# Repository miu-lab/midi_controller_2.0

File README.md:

# MIDI Controller

MIDI Controller est un projet de contrôleur MIDI pour la plateforme Teensy, utilisant PlatformIO pour la gestion du projet et la compilation. Il offre une architecture modulaire et extensible pour le développement d'applications de contrôle MIDI.

## Vue d'ensemble

Ce projet implémente un contrôleur MIDI complet avec:
- Support pour encodeurs rotatifs, boutons et autres contrôles
- Affichage OLED pour l'interface utilisateur
- Communication MIDI via USB
- Gestion de profils et configurations personnalisables

## Architecture

Le projet est organisé selon une architecture hexagonale (aussi appelée architecture en oignon) avec injection de dépendances:

### Couches Principales

- **Core** : Contient la logique métier principale, indépendante de l'implémentation
  - **Domain** : Définitions des entités et interfaces principales
  - **Use Cases** : Implémentation des cas d'utilisation
  - **Ports** : Interfaces pour les adaptateurs
  - **Interfaces** : Contrats abstraits pour les sous-systèmes

- **Adapters** : Implémentations concrètes des interfaces
  - **Primary** : Adaptateurs d'entrée (UI, contrôles)
  - **Secondary** : Adaptateurs de sortie (MIDI, stockage)

- **App** : Point d'entrée de l'application et orchestration
  - **Subsystems** : Sous-systèmes modulaires encapsulant des fonctionnalités complètes
  - **DI** : Système d'injection de dépendances moderne

### Sous-systèmes

L'application est divisée en sous-systèmes indépendants, chacun implémentant une interface abstraite:

- **ConfigurationSubsystem** (`IConfiguration`): Gestion des paramètres et préférences
- **InputSubsystem** (`IInputSystem`): Traitement des entrées utilisateur
- **MidiSubsystem** (`IMidiSystem`): Communication MIDI et mapping
- **UISubsystem** (`IUISystem`): Interface utilisateur et affichage

## Fonctionnalités Principales

- **Mapping MIDI flexible**: Assignez facilement des contrôles à différents messages MIDI
- **Interface utilisateur intuitive**: Navigation par menus sur écran OLED
- **Profils multiples**: Sauvegardez et chargez différentes configurations
- **Mode d'apprentissage**: Apprenez facilement de nouveaux mappings MIDI
- **Modularité**: Ajoutez de nouvelles fonctionnalités sans modifier le code existant

## Compilation et Déploiement

### Prérequis
- PlatformIO
- Teensy Loader
- Librairies Arduino requises (voir platformio.ini)

### Compilation
```bash
pio run
```

### Upload vers le Teensy
```bash
pio run -t upload
```

### Moniteur Série
```bash
pio device monitor
```

## Tests

Le projet comprend une infrastructure de tests unitaires et d'intégration basée sur Unity:

```bash
pio test
```

Les tests couvrent les composants individuels ainsi que l'intégration des sous-systèmes.

## Contribution

Les contributions sont les bienvenues! Veuillez consulter [CONTRIBUTING.md](CONTRIBUTING.md) pour les lignes directrices sur la façon de contribuer au projet.

## Licence

Ce projet est sous licence MIT. Voir le fichier LICENSE pour plus de détails.

## Contact

Pour toute question ou suggestion, veuillez ouvrir une issue sur le dépôt GitHub du projet.

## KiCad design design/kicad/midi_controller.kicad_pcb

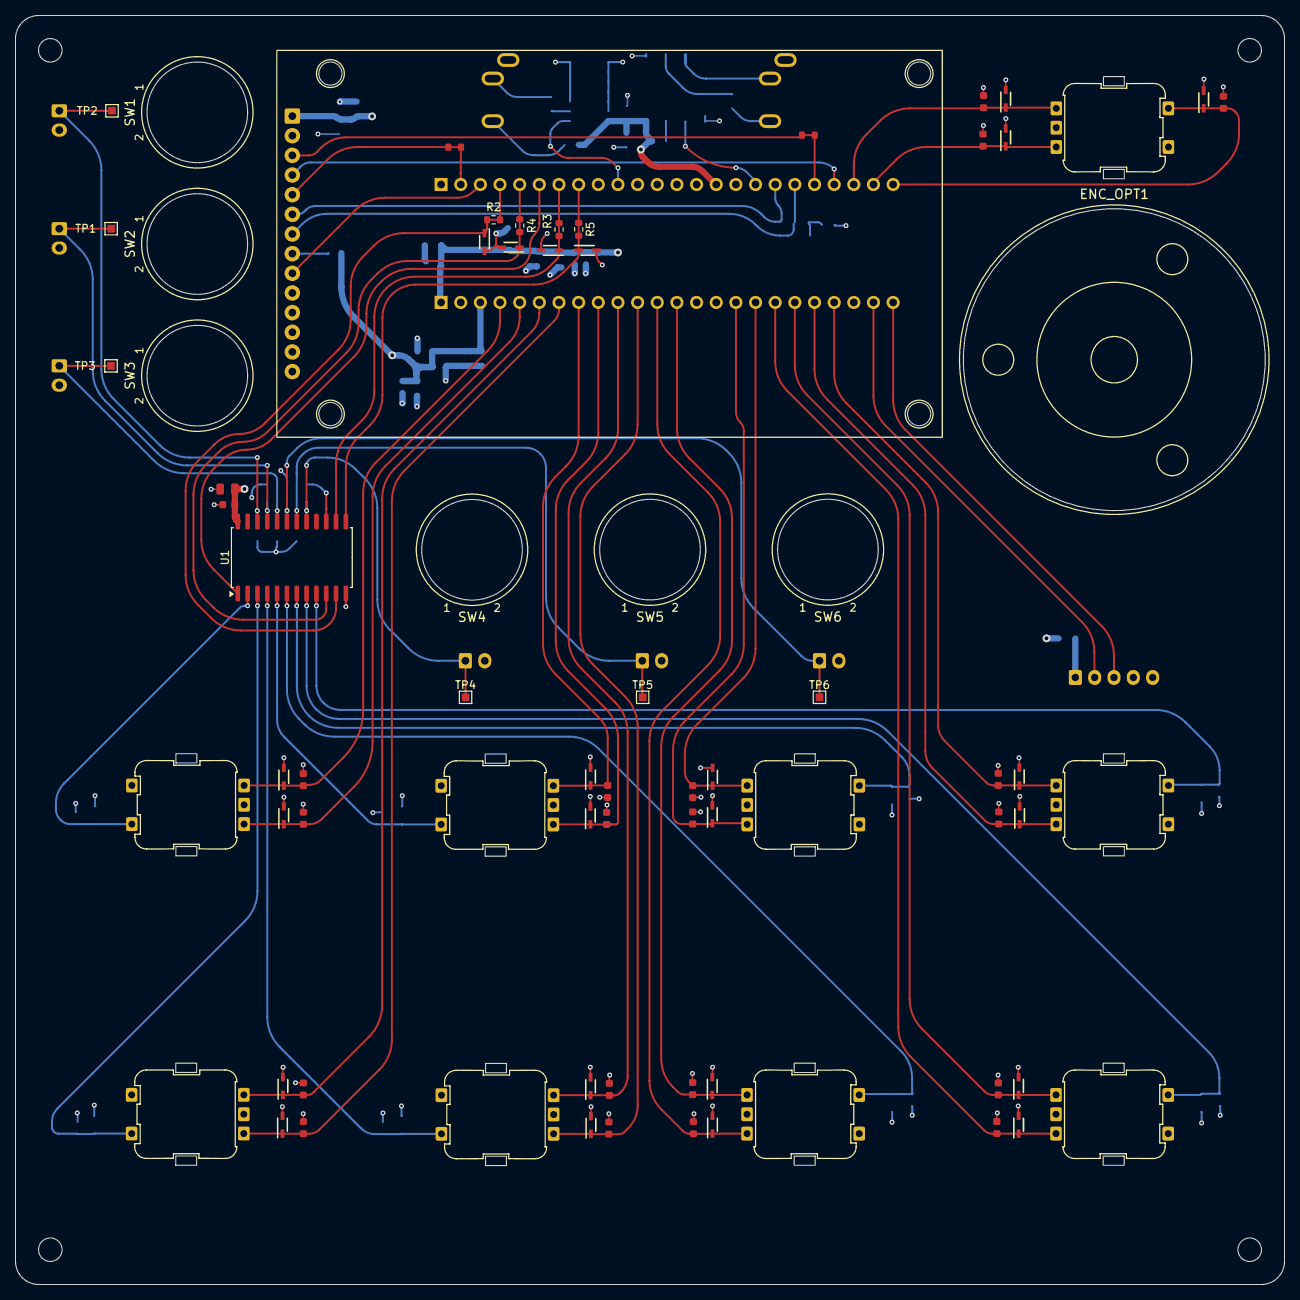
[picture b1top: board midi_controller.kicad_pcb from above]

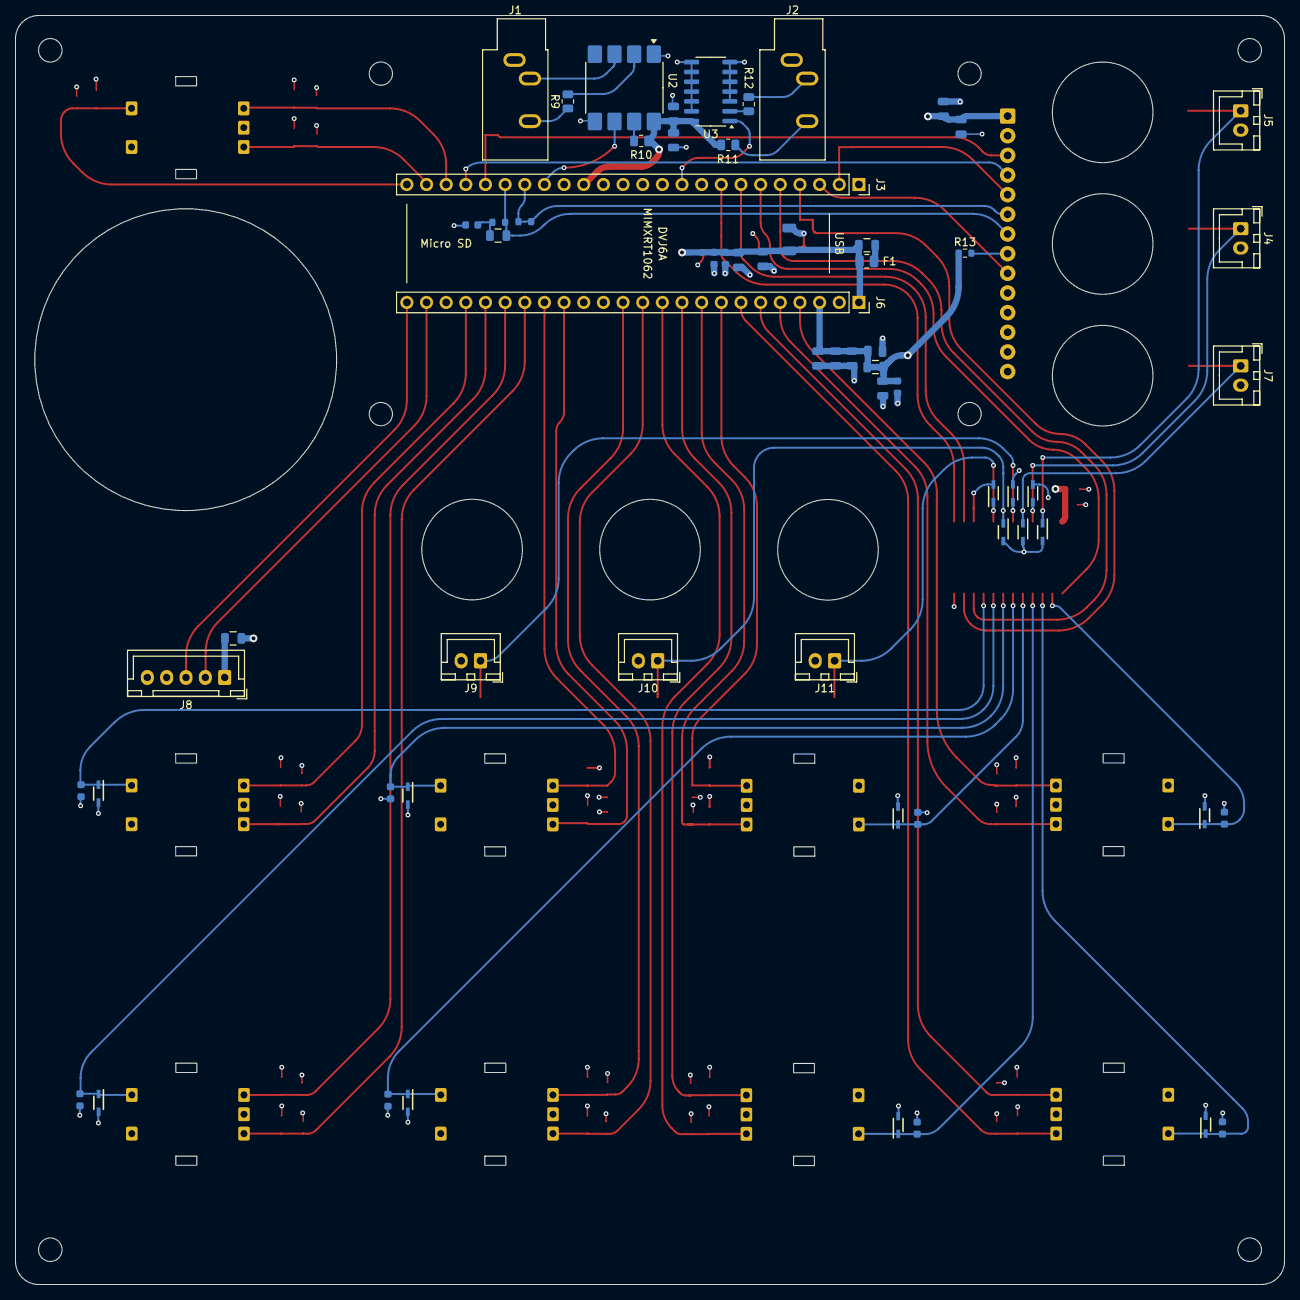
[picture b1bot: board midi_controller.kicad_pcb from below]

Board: 4 copper layers, 164.0 x 164.0 mm, 138 parts (64 on the bottom side), 63 nets.

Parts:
C1, C2, C3, C5, C6, C7, C8, C9, C10, C11, C12, C13, C14, C15, C16, C17, C18, C19, C20, C21, C38, C39, C40, C41, C42, C43, C44, C45: 100nF; C_0603
C4, C31, C35: 10uF; C_0805
C22: 100pF; C_0603
C23: 100uF; C_1206
C24, C37: 1nF; C_0603
C25, C26, C28, C30, C32, C34, C36: 100nF; C_0805
C27, C33: 47uF; C_0805
C29: 10nF; C_0603
D1, D2, D3, D4, D5, D6, D7, D8, D9, D10, D11, D12, D13, D14, D15, D16, D17, D18, D19, D20, D21, D22, D23, D24, D25, D26, D27, D28, D29, D30, D31, D32, D33, D34, D35, D36, D37: PESD5V0L1BA,115; SOD2512X110N
DISP1: MIDI_Display_MSP2807; MSP2807_ILI9341_Display
ENC_MECH1, ENC_MECH2, ENC_MECH3, ENC_MECH4, ENC_MECH5, ENC_MECH6, ENC_MECH7, ENC_MECH8, ENC_MECH9: MIDI_Encoder_PEC11R; PEC11R4220FS0024
ENC_OPT1: MIDI_Encoder_E38S6G5_Optical; E38S6G5_Optical_Encoder
F1: Fuse; Fuse_0805_2012Metric
FB1, FB2, FB3, FB4: FB_0805
J1: MIDI In; Jack_3.5mm_CUI_SJ1-3533NG_Horizontal
J2: MIDI Out; Jack_3.5mm_CUI_SJ1-3533NG_Horizontal
J3, J6: Conn_01x24_Socket; PinSocket_1x24_P2.54mm_Vertical
J4, J5, J7, J9, J10, J11: Conn_01x02_Socket; JST_XH_B2B-XH-A_1x02_P2.50mm_Vertical_JLC_Constraints
J8: Conn_01x05; JST_XH_B5B-XH-A_1x05_P2.50mm_Vertical
MCU1: MIDI_Teensy4.1; Teensy41_Mechanical
R1, R6, R7, R8: 33Ω; R_0603
R2, R3, R4, R5: 100; R_0603_1608Metric
R9, R11, R12: 220; R_0805_2012Metric
R10: 1k; R_0805_2012Metric
R13: 220; R_0603_1608Metric
SW1, SW2, SW3, SW4, SW5, SW6: PV0H24011_Pushbutton
TP1, TP2, TP3, TP4, TP5, TP6: TestPoint; TestPoint_Pad_1.0x1.0mm
U1: CD74HC4067M; SOIC-24W_7.5x15.4mm_P1.27mm
U2: 6N137; SOP-8_6.605x9.655mm_P2.54mm
U3: 74HC14D,653; SOIC-14_L8.7-W3.9-P1.27-LS6.0-BL

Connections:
+3V3_A: C4.1, C5.1, C32.1, C33.1, C34.1, C35.1, C36.1, C37.1, FB3.1, FB3.2, J6.3, R13.1, U1.24 (VCC)
+3V3_B: C26.1, C28.2, J3.15, R10.2, R11.1, U2.8 (VCC), U3.14 (VCC)
+5V: C23.1, C24.1, C25.1, C27.1, C29.1, C30.2, C31.1, DISP1.1 (VCC), F1.1, FB2.1, FB4.2, J6.1
/Buttons_Momentary/BUTTON_PUSH_MOM_01: D26.1 (K1), J5.1, TP2.1, U1.22 (I9)
/Buttons_Momentary/BUTTON_PUSH_MOM_02: D29.1 (K1), J4.1, TP1.1, U1.21 (I10)
/Buttons_Momentary/BUTTON_PUSH_MOM_03: D28.1 (K1), J7.1, TP3.1, U1.20 (I11)
/Buttons_Momentary/BUTTON_PUSH_MOM_04: D27.1 (K1), J9.1, TP6.1, U1.19 (I12)
/Buttons_Momentary/BUTTON_PUSH_MOM_05: D24.1 (K1), J10.1, TP5.1, U1.18 (I13)
/Buttons_Momentary/BUTTON_PUSH_MOM_06: D25.1 (K1), J11.1, TP4.1, U1.17 (I14)
/COM: J3.6, U1.1 (COM)
/CS: DISP1.3 (CS), J3.20, R6.1, R6.2
/DC: DISP1.5 (DC), J3.2, R1.1, R1.2
/LED: DISP1.8 (LED), R13.2
/MIDI_Encoder_Matrix_2x4_with_push_buttons/1x1.QUAD_A: C7.2, D9.1 (K1), ENC_MECH2.A, J6.5
/MIDI_Encoder_Matrix_2x4_with_push_buttons/1x1.QUAD_B: C6.2, D8.1 (K1), ENC_MECH2.B, J6.4
/MIDI_Encoder_Matrix_2x4_with_push_buttons/1x1_SW_A: C41.2, D33.1 (K1), ENC_MECH2.1 (SW1), U1.2 (I7)
/MIDI_Encoder_Matrix_2x4_with_push_buttons/1x2.QUAD_A: C8.2, D11.1 (K1), ENC_MECH3.A, J6.9
/MIDI_Encoder_Matrix_2x4_with_push_buttons/1x2.QUAD_B: C9.2, D10.1 (K1), ENC_MECH3.B, J6.8
/MIDI_Encoder_Matrix_2x4_with_push_buttons/1x2_SW_A: C40.2, D32.1 (K1), ENC_MECH3.1 (SW1), U1.5 (I4)
/MIDI_Encoder_Matrix_2x4_with_push_buttons/1x3.QUAD_A: C10.2, D12.1 (K1), ENC_MECH4.A, J6.17
/MIDI_Encoder_Matrix_2x4_with_push_buttons/1x3.QUAD_B: C11.2, D13.1 (K1), ENC_MECH4.B, J6.16
/MIDI_Encoder_Matrix_2x4_with_push_buttons/1x3_SW_A: C39.2, D31.1 (K1), ENC_MECH4.1 (SW1), U1.7 (I2)
/MIDI_Encoder_Matrix_2x4_with_push_buttons/1x4.QUAD_A: C12.2, D14.1 (K1), ENC_MECH5.A, J6.21
/MIDI_Encoder_Matrix_2x4_with_push_buttons/1x4.QUAD_B: C13.2, D15.1 (K1), ENC_MECH5.B, J6.20
/MIDI_Encoder_Matrix_2x4_with_push_buttons/1x4_SW_A: C38.2, D30.1 (K1), ENC_MECH5.1 (SW1), U1.9 (I0)
/MIDI_Encoder_Matrix_2x4_with_push_buttons/2x1.QUAD_A: C14.2, D17.1 (K1), ENC_MECH6.A, J6.7
/MIDI_Encoder_Matrix_2x4_with_push_buttons/2x1.QUAD_B: C15.2, D16.1 (K1), ENC_MECH6.B, J6.6
/MIDI_Encoder_Matrix_2x4_with_push_buttons/2x1_SW_A: C45.2, D37.1 (K1), ENC_MECH6.1 (SW1), U1.3 (I6)
/MIDI_Encoder_Matrix_2x4_with_push_buttons/2x2.QUAD_A: C16.2, D18.1 (K1), ENC_MECH7.A, J6.11
/MIDI_Encoder_Matrix_2x4_with_push_buttons/2x2.QUAD_B: C17.2, D19.1 (K1), ENC_MECH7.B, J6.10
/MIDI_Encoder_Matrix_2x4_with_push_buttons/2x2_SW_A: C44.2, D36.1 (K1), ENC_MECH7.1 (SW1), U1.4 (I5)
/MIDI_Encoder_Matrix_2x4_with_push_buttons/2x3.QUAD_A: C19.2, D20.1 (K1), ENC_MECH8.A, J6.13
/MIDI_Encoder_Matrix_2x4_with_push_buttons/2x3.QUAD_B: C18.2, D21.1 (K1), ENC_MECH8.B, J6.12
/MIDI_Encoder_Matrix_2x4_with_push_buttons/2x3_SW_A: C43.2, D35.1 (K1), ENC_MECH8.1 (SW1), U1.6 (I3)
/MIDI_Encoder_Matrix_2x4_with_push_buttons/2x4.QUAD_A: C20.2, D22.1 (K1), ENC_MECH9.A, J6.19
/MIDI_Encoder_Matrix_2x4_with_push_buttons/2x4.QUAD_B: C21.2, D23.1 (K1), ENC_MECH9.B, J6.18
/MIDI_Encoder_Matrix_2x4_with_push_buttons/2x4_SW_A: C42.2, D34.1 (K1), ENC_MECH9.1 (SW1), U1.8 (I1)
/MISO: DISP1.9 (SDO/MISO), J3.3
/MOSI: DISP1.6 (SDI/MOSI), J3.18, R8.1, R8.2
/NAV.QUAD_A: C1.2, D1.1 (K1), ENC_MECH1.A, J3.22
/NAV.QUAD_B: C2.2, D7.1 (K1), ENC_MECH1.B, J3.23
/NAV.SW: C3.2, D2.1 (K1), ENC_MECH1.1 (SW1), J3.24
/OPT.QUAD_A: J6.23, J8.2
/OPT.QUAD_B: J6.24, J8.3
/RST: DISP1.4 (RST), J3.21
/RX6: J3.17, U2.6 (VO)
/S0: D5.1 (K1), J3.5, R4.1, R4.2, U1.10 (S0)
/S1: D3.1 (K1), J3.4, R2.1, R2.2, U1.11 (S1)
/S2: D6.1 (K1), J3.7, R3.1, R3.2, U1.14 (S2)
/S3: D4.1 (K1), J3.8, R5.1, R5.2, U1.13 (S3)
/SCK: DISP1.7 (SCK), FB1.1, J3.19, R7.2
/TX2: J3.10, U3.1 (1A)
GND: C1.1, C2.1, C3.1, C4.2, C5.2, C6.1, C7.1, C8.1, C9.1, C10.1, C11.1, C12.1, C13.1, C14.1, C15.1, C16.1, C17.1, C18.1, C19.1, C20.1, C21.1, C22.2, C23.2, C24.2, C25.2, C26.2, C27.2, C28.1, C29.2, C30.1, C31.2, C32.2, C33.2, C34.2, C35.2, C36.2, C37.2, C38.1, C39.1, C40.1, C41.1, C42.1, C43.1, C44.1, C45.1, D1.2 (K2), D2.2 (K2), D3.2 (K2), D4.2 (K2), D5.2 (K2), D6.2 (K2), D7.2 (K2), D8.2 (K2), D9.2 (K2), D10.2 (K2), D11.2 (K2), D12.2 (K2), D13.2 (K2), D14.2 (K2), D15.2 (K2), D16.2 (K2), D17.2 (K2), D18.2 (K2), D19.2 (K2), D20.2 (K2), D21.2 (K2), D22.2 (K2), D23.2 (K2), D24.2 (K2), D25.2 (K2), D26.2 (K2), D27.2 (K2), D28.2 (K2), D29.2 (K2), D30.2 (K2), D31.2 (K2), D32.2 (K2), D33.2 (K2), D34.2 (K2), D35.2 (K2), D36.2 (K2), D37.2 (K2), DISP1.2 (GND), ENC_MECH1.2 (GND), ENC_MECH1.C (GND), ENC_MECH2.2 (GND), ENC_MECH2.C (GND), ENC_MECH3.2 (GND), ENC_MECH3.C (GND), ENC_MECH4.2 (GND), ENC_MECH4.C (GND), ENC_MECH5.2 (GND), ENC_MECH5.C (GND), ENC_MECH6.2 (GND), ENC_MECH6.C (GND), ENC_MECH7.2 (GND), ENC_MECH7.C (GND), ENC_MECH8.2 (GND), ENC_MECH8.C (GND), ENC_MECH9.2 (GND), ENC_MECH9.C (GND), J1.S, J2.S, J3.1, J4.2, J5.2, J6.2, J6.15, J7.2, J8.4, J8.5, J9.2, J10.2, J11.2, U1.12 (GND), U1.15 (~E), U2.1 (NC), U2.5 (GND), U3.3 (2A), U3.4 (2Y), U3.5 (3A), U3.6 (3Y), U3.7 (GND), U3.8 (4Y), U3.9 (4A), U3.10 (5Y), U3.11 (5A), U3.12 (6Y), U3.13 (6A)
unnamed: C22.1, FB1.2, R7.1
unnamed: F1.2, FB2.2
unnamed: J1.R, R9.1
unnamed: J2.R, R11.2
unnamed: J2.T, R12.2
unnamed: FB4.1, J8.1
unnamed: R9.2, U2.2 (A)
unnamed: J1.T, U2.3 (C)
unnamed: R10.1, U2.7 (EN)
unnamed: R12.1, U3.2 (1Y)

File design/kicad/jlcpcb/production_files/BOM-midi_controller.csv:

Comment,Designator,Footprint,LCSC,Quantity
~,"FB1,FB2,FB3,FB4",FB_0805,C1015,4
100nF,"C1,C10,C11,C12,C13,C14,C15,C16,C17,C18,C19,C2,C20,C21,C3,C38,C39,C40,C41,C42,C43,C44,C45,C5,C6,C7,C8,C9",C_0603,C14663,28
100pF,C22,C_0603,C14858,1
100uF,C23,C_1206,C15008,1
6N137,U2,SOP-8_6.605x9.655mm_P2.54mm,C15825,1
10uF,"C31,C35,C4",C_0805,C15850,3
1nF,"C24,C37",C_0603,C1588,2
47uF,"C27,C33",C_0805,C16780,2
1k,R10,R_0805_2012Metric,C17513,1
220,"R11,R12,R9",R_0805_2012Metric,C17557,3
100,"R2,R3,R4,R5",R_0603_1608Metric,C22775,4
220,R13,R_0603_1608Metric,C22962,1
33Ω,"R1,R6,R7,R8",R_0603,C23140,4
100nF,"C25,C26,C28,C30,C32,C34,C36",C_0805,C28233,7
Conn_01x02_Socket,"J10,J11,J4,J5,J7,J9",JST_XH_B2B-XH-A_1x02_P2.50mm_Vertical_JLC_Constraints,C2908600,6
Conn_01x05,J8,JST_XH_B5B-XH-A_1x05_P2.50mm_Vertical,C2908603,1
Conn_01x24_Socket,"J3,J6",PinSocket_1x24_P2.54mm_Vertical,C41376163,2
CD74HC4067M,U1,SOIC-24W_7.5x15.4mm_P1.27mm,C496123,1
"74HC14D,653",U3,SOIC-14_L8.7-W3.9-P1.27-LS6.0-BL,C5605,1
10nF,C29,C_0603,C57112,1
"PESD5V0L1BA,115","D1,D10,D11,D12,D13,D14,D15,D16,D17,D18,D19,D2,D20,D21,D22,D23,D24,D25,D26,D27,D28,D29,D3,D30,D31,D32,D33,D34,D35,D36,D37,D4,D5,D6,D7,D8,D9",SOD2512X110N,C85380,37
Fuse,F1,Fuse_0805_2012Metric,C883101,1

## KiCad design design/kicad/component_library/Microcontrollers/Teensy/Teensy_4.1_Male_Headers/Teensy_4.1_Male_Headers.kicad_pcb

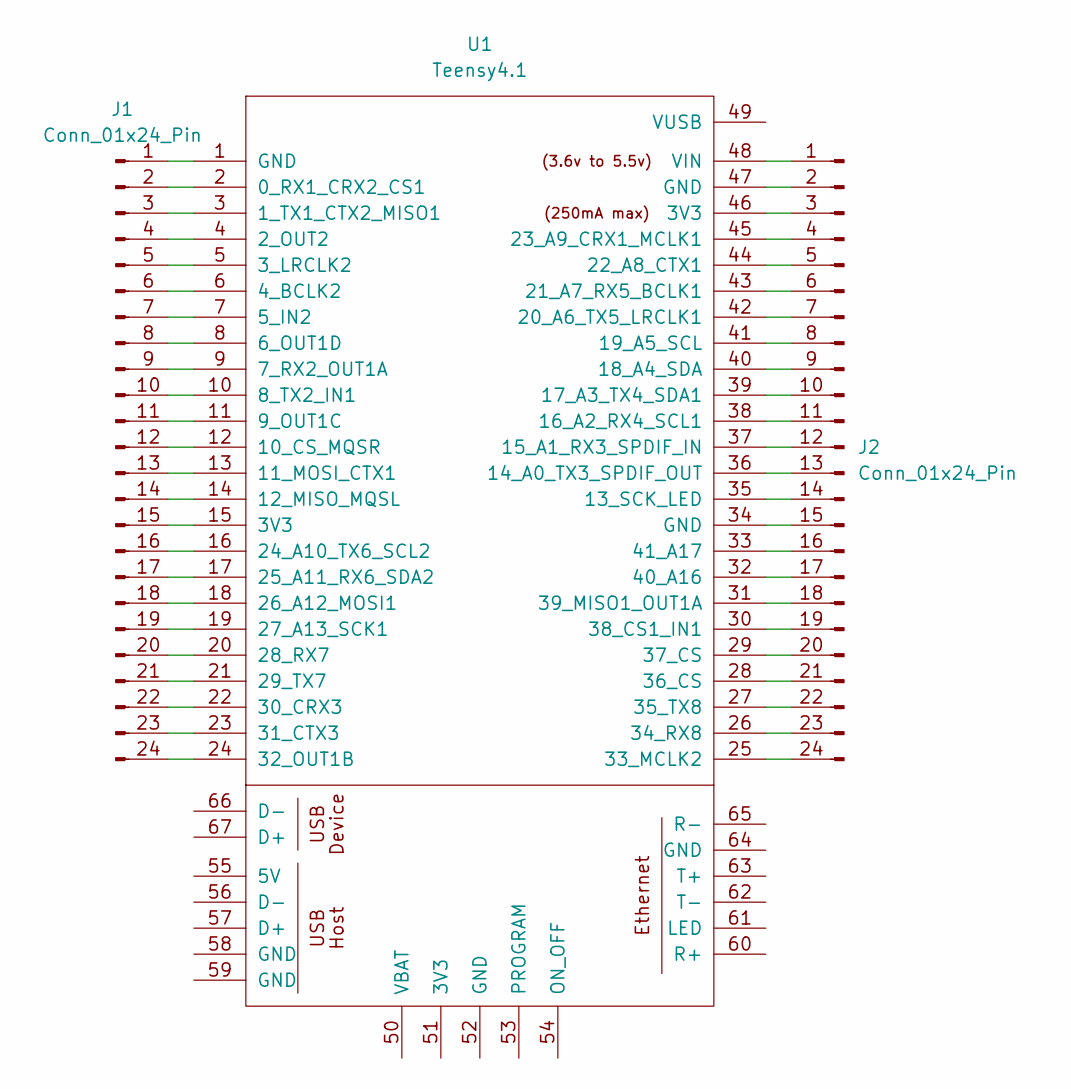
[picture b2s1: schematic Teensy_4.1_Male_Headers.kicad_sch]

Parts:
J1, J2: Conn_01x24_Pin; PinHeader_1x24_P2.54mm_Vertical
U1: Teensy4.1; Teensy41

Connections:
unnamed: J1.1, U1.1 (GND)
unnamed: J1.2, U1.2 (0_RX1_CRX2_CS1)
unnamed: J1.3, U1.3 (1_TX1_CTX2_MISO1)
unnamed: J1.4, U1.4 (2_OUT2)
unnamed: J1.5, U1.5 (3_LRCLK2)
unnamed: J1.6, U1.6 (4_BCLK2)
unnamed: J1.7, U1.7 (5_IN2)
unnamed: J1.8, U1.8 (6_OUT1D)
unnamed: J1.9, U1.9 (7_RX2_OUT1A)
unnamed: J1.10, U1.10 (8_TX2_IN1)
unnamed: J1.11, U1.11 (9_OUT1C)
unnamed: J1.12, U1.12 (10_CS_MQSR)
unnamed: J1.13, U1.13 (11_MOSI_CTX1)
unnamed: J1.14, U1.14 (12_MISO_MQSL)
unnamed: J1.15, U1.15 (3V3)
unnamed: J1.16, U1.16 (24_A10_TX6_SCL2)
unnamed: J1.17, U1.17 (25_A11_RX6_SDA2)
unnamed: J1.18, U1.18 (26_A12_MOSI1)
unnamed: J1.19, U1.19 (27_A13_SCK1)
unnamed: J1.20, U1.20 (28_RX7)
unnamed: J1.21, U1.21 (29_TX7)
unnamed: J1.22, U1.22 (30_CRX3)
unnamed: J1.23, U1.23 (31_CTX3)
unnamed: J1.24, U1.24 (32_OUT1B)
unnamed: J2.1, U1.48 (VIN)
unnamed: J2.2, U1.47 (GND)
unnamed: J2.3, U1.46 (3V3)
unnamed: J2.4, U1.45 (23_A9_CRX1_MCLK1)
unnamed: J2.5, U1.44 (22_A8_CTX1)
unnamed: J2.6, U1.43 (21_A7_RX5_BCLK1)
unnamed: J2.7, U1.42 (20_A6_TX5_LRCLK1)
unnamed: J2.8, U1.41 (19_A5_SCL)
unnamed: J2.9, U1.40 (18_A4_SDA)
unnamed: J2.10, U1.39 (17_A3_TX4_SDA1)
unnamed: J2.11, U1.38 (16_A2_RX4_SCL1)
unnamed: J2.12, U1.37 (15_A1_RX3_SPDIF_IN)
unnamed: J2.13, U1.36 (14_A0_TX3_SPDIF_OUT)
unnamed: J2.14, U1.35 (13_SCK_LED)
unnamed: J2.15, U1.34 (GND)
unnamed: J2.16, U1.33 (41_A17)
unnamed: J2.17, U1.32 (40_A16)
unnamed: J2.18, U1.31 (39_MISO1_OUT1A)
unnamed: J2.19, U1.30 (38_CS1_IN1)
unnamed: J2.20, U1.29 (37_CS)
unnamed: J2.21, U1.28 (36_CS)
unnamed: J2.22, U1.27 (35_TX8)
unnamed: J2.23, U1.26 (34_RX8)
unnamed: J2.24, U1.25 (33_MCLK2)

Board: 2 copper layers, 3 parts (2 on the bottom side), 48 nets, no tracks yet.

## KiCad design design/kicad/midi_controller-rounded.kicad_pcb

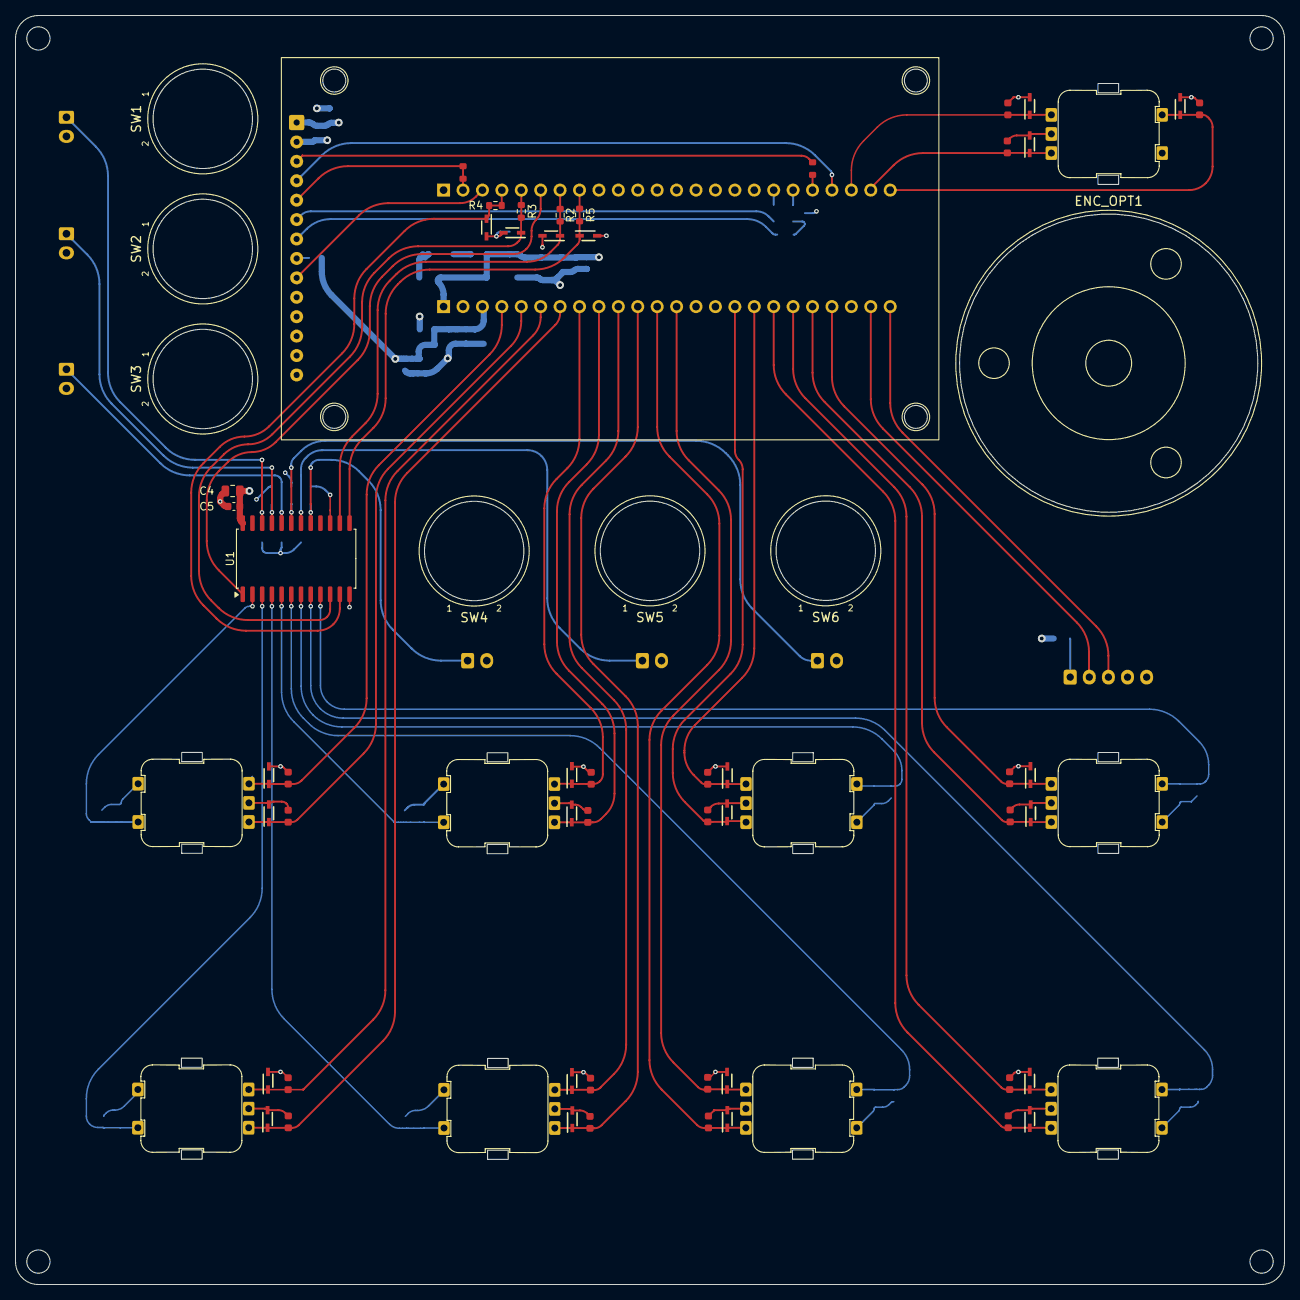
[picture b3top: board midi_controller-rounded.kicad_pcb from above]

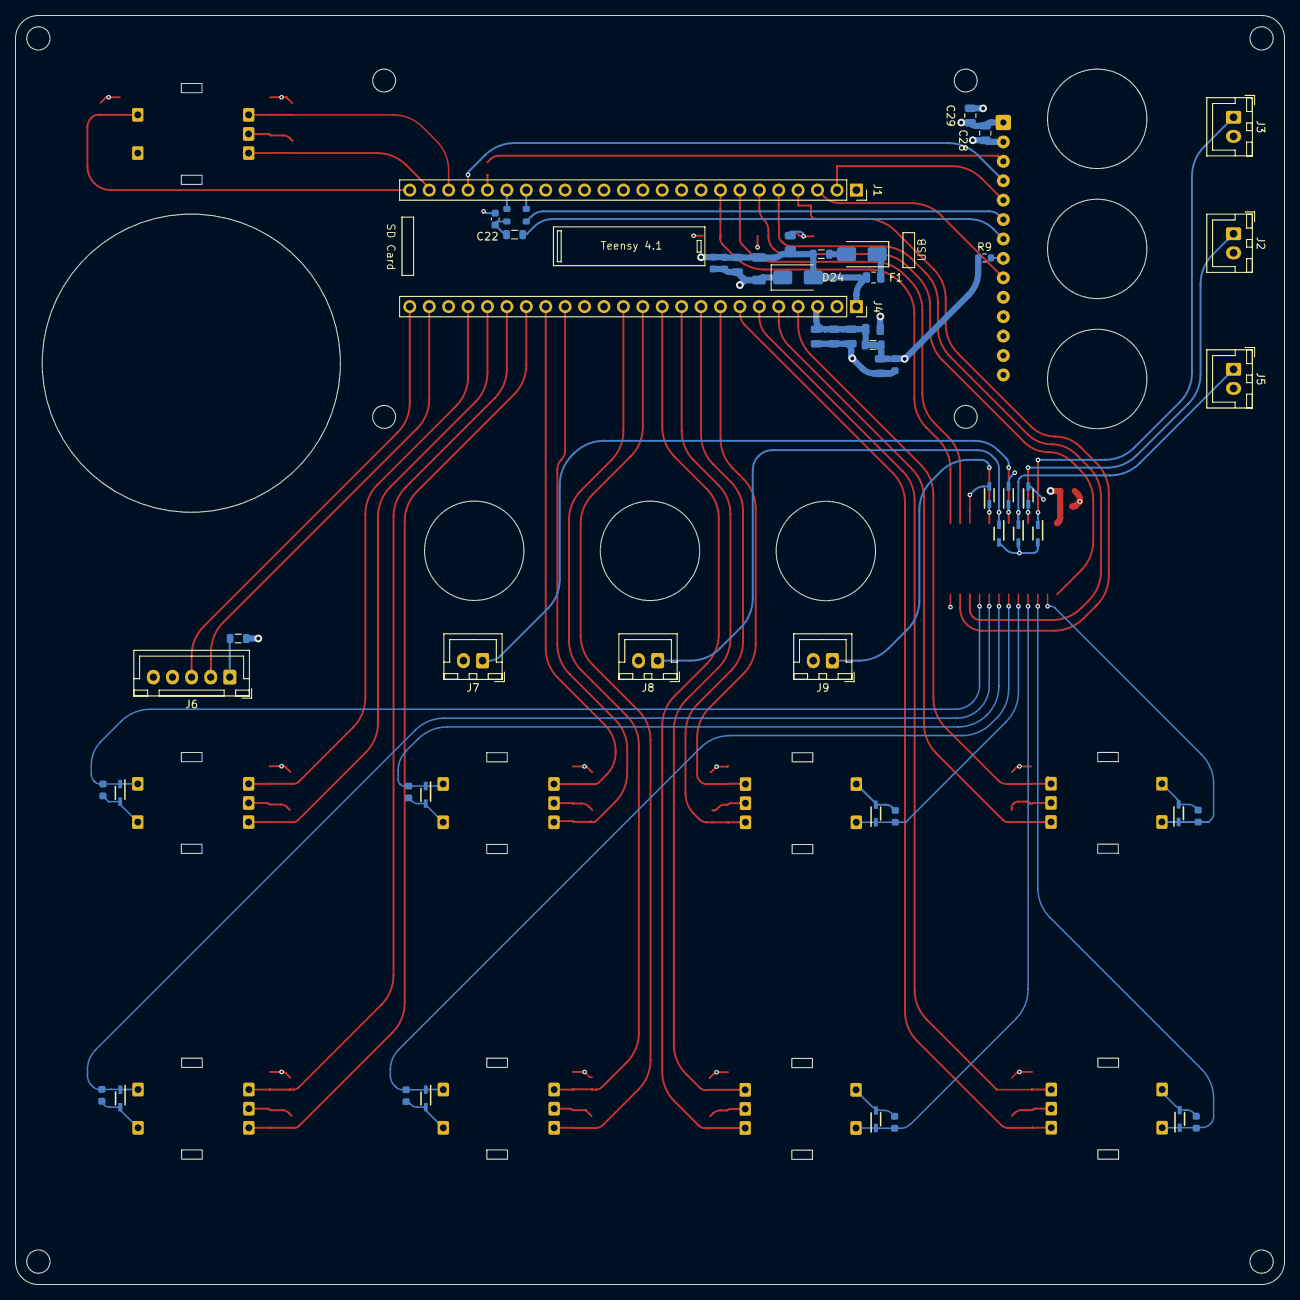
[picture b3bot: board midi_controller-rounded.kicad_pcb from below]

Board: 4 copper layers, 166.0 x 166.0 mm, 123 parts (55 on the bottom side), 57 nets.

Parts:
C1, C2, C3, C6, C7, C8, C9, C10, C11, C12, C13, C14, C15, C16, C17, C18, C19, C20, C21, C36, C37, C38, C39, C40, C41, C42, C43: 100nF; C_0603
C4, C29: 10u; C_0805_2012Metric
C5: 100n; C_0603_1608Metric
C22: 100p; C_0603_1608Metric
C23, C32, C33, C35: 100nF; C_0805
C24: 10nF; C_0603
C25, C31: 47uF; C_0805
C26: 100uF; C_1206
C27, C34: 1nF; C_0603
C28: 100n; C_0805_2012Metric
C30: 10uF; C_0805
D1, D2, D3, D4, D5, D6, D7, D8, D9, D10, D11, D12, D13, D14, D15, D16, D17, D18, D19, D20, D21, D22, D23, D26, D27, D28, D29, D30, D31, D32, D33, D34, D35, D36, D37, D38, D39: PESD5V0L1BA,115; SOD2512X110N
D24: SMAJ5.0CA; D_SMA
D25: SS34; D_SMA
DISP1: MIDI_Display_MSP2807; MSP2807_ILI9341_Display
ENC_MECH1, ENC_MECH2, ENC_MECH3, ENC_MECH4, ENC_MECH5, ENC_MECH6, ENC_MECH7, ENC_MECH8, ENC_MECH9: MIDI_Encoder_PEC11R; PEC11R4220FS0024
ENC_OPT1: MIDI_Encoder_E38S6G5_Optical; E38S6G5_Optical_Encoder
F1: Fuse; Fuse_0805_2012Metric
FB1, FB2, FB3, FB4: FB_0805
J1, J4: Conn_01x24_Socket; PinSocket_1x24_P2.54mm_Vertical
J2, J3, J5, J7, J8, J9: Conn_01x02_Socket; JST_XH_B2B-XH-A_1x02_P2.50mm_Vertical
J6: Conn_01x05; JST_XH_B5B-XH-A_1x05_P2.50mm_Vertical
R1, R6, R7, R8: 33Ω; R_0603
R2, R3, R4, R5: 100; R_0603_1608Metric
R9: 220; R_0603_1608Metric
SW1, SW2, SW3, SW4, SW5, SW6: PV0H24011_Pushbutton
U1: CD74HC4067M; SOIC-24W_7.5x15.4mm_P1.27mm

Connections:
+3V3: C4.1, C5.1, C30.1, C31.1, C32.1, C33.1, C34.1, C35.1, FB3.1, FB3.2, J4.3, R9.1, U1.24 (VCC)
+5V: C23.1, C24.1, C25.1, C26.1, C27.1, C28.2, C29.1, D24.2 (A2), DISP1.1 (VCC), F1.1, FB2.1, FB4.2, J4.1
/Buttons_Momentary/BUTTON_PUSH_MOM_01: D28.1 (K1), J3.1, U1.22 (I9)
/Buttons_Momentary/BUTTON_PUSH_MOM_02: D29.1 (K1), J2.1, U1.21 (I10)
/Buttons_Momentary/BUTTON_PUSH_MOM_03: D31.1 (K1), J5.1, U1.20 (I11)
/Buttons_Momentary/BUTTON_PUSH_MOM_04: D30.1 (K1), J7.1, U1.19 (I12)
/Buttons_Momentary/BUTTON_PUSH_MOM_05: D27.1 (K1), J8.1, U1.18 (I13)
/Buttons_Momentary/BUTTON_PUSH_MOM_06: D26.1 (K1), J9.1, U1.17 (I14)
/COM: J1.6, U1.1 (COM)
/CS: DISP1.3 (CS), R6.1
/DC: DISP1.5 (DC), J1.2, R1.1, R1.2
/LED: DISP1.8 (LED), R9.2
/MIDI_Encoder_Matrix_2x4_with_push_buttons/1x1.QUAD_A: C7.2, D9.1 (K1), ENC_MECH2.A, J4.5
/MIDI_Encoder_Matrix_2x4_with_push_buttons/1x1.QUAD_B: C6.2, D8.1 (K1), ENC_MECH2.B, J4.4
/MIDI_Encoder_Matrix_2x4_with_push_buttons/1x1_SW_A: C39.2, D35.1 (K1), ENC_MECH2.1 (SW1), U1.2 (I7)
/MIDI_Encoder_Matrix_2x4_with_push_buttons/1x2.QUAD_A: C8.2, D10.1 (K1), ENC_MECH3.A, J4.9
/MIDI_Encoder_Matrix_2x4_with_push_buttons/1x2.QUAD_B: C9.2, D11.1 (K1), ENC_MECH3.B, J4.8
/MIDI_Encoder_Matrix_2x4_with_push_buttons/1x2_SW_A: C38.2, D34.1 (K1), ENC_MECH3.1 (SW1), U1.5 (I4)
/MIDI_Encoder_Matrix_2x4_with_push_buttons/1x3.QUAD_A: C11.2, D12.1 (K1), ENC_MECH4.A, J4.17
/MIDI_Encoder_Matrix_2x4_with_push_buttons/1x3.QUAD_B: C10.2, D13.1 (K1), ENC_MECH4.B, J4.16
/MIDI_Encoder_Matrix_2x4_with_push_buttons/1x3_SW_A: C37.2, D33.1 (K1), ENC_MECH4.1 (SW1), U1.7 (I2)
/MIDI_Encoder_Matrix_2x4_with_push_buttons/1x4.QUAD_A: C12.2, D15.1 (K1), ENC_MECH5.A, J4.21
/MIDI_Encoder_Matrix_2x4_with_push_buttons/1x4.QUAD_B: C13.2, D14.1 (K1), ENC_MECH5.B, J4.20
/MIDI_Encoder_Matrix_2x4_with_push_buttons/1x4_SW_A: C36.2, D32.1 (K1), ENC_MECH5.1 (SW1), U1.9 (I0)
/MIDI_Encoder_Matrix_2x4_with_push_buttons/2x1.QUAD_A: C14.2, D16.1 (K1), ENC_MECH6.A, J4.7
/MIDI_Encoder_Matrix_2x4_with_push_buttons/2x1.QUAD_B: C15.2, D17.1 (K1), ENC_MECH6.B, J4.6
/MIDI_Encoder_Matrix_2x4_with_push_buttons/2x1_SW_A: C43.2, D39.1 (K1), ENC_MECH6.1 (SW1), U1.3 (I6)
/MIDI_Encoder_Matrix_2x4_with_push_buttons/2x2.QUAD_A: C16.2, D19.1 (K1), ENC_MECH7.A, J4.11
/MIDI_Encoder_Matrix_2x4_with_push_buttons/2x2.QUAD_B: C17.2, D18.1 (K1), ENC_MECH7.B, J4.10
/MIDI_Encoder_Matrix_2x4_with_push_buttons/2x2_SW_A: C42.2, D38.1 (K1), ENC_MECH7.1 (SW1), U1.4 (I5)
/MIDI_Encoder_Matrix_2x4_with_push_buttons/2x3.QUAD_A: C18.2, D21.1 (K1), ENC_MECH8.A, J4.13
/MIDI_Encoder_Matrix_2x4_with_push_buttons/2x3.QUAD_B: C19.2, D20.1 (K1), ENC_MECH8.B, J4.12
/MIDI_Encoder_Matrix_2x4_with_push_buttons/2x3_SW_A: C41.2, D37.1 (K1), ENC_MECH8.1 (SW1), U1.6 (I3)
/MIDI_Encoder_Matrix_2x4_with_push_buttons/2x4.QUAD_A: C20.2, D22.1 (K1), ENC_MECH9.A, J4.19
/MIDI_Encoder_Matrix_2x4_with_push_buttons/2x4.QUAD_B: C21.2, D23.1 (K1), ENC_MECH9.B, J4.18
/MIDI_Encoder_Matrix_2x4_with_push_buttons/2x4_SW_A: C40.2, D36.1 (K1), ENC_MECH9.1 (SW1), U1.8 (I1)
/MISO: DISP1.9 (SDO/MISO), J1.3
/MOSI: DISP1.6 (SDI/MOSI), R8.1
/NAV.QUAD_A: C2.2, D1.1 (K1), ENC_MECH1.A, J1.22
/NAV.QUAD_B: C1.2, D7.1 (K1), ENC_MECH1.B, J1.23
/NAV.SW: C3.2, D2.1 (K1), ENC_MECH1.1 (SW1), J1.24
/OPT.QUAD_A: J4.23, J6.2
/OPT.QUAD_B: J4.24, J6.3
/RST: DISP1.4 (RST), J1.21
/S0: D4.1 (K1), J1.5, R3.1, R3.2, U1.10 (S0)
/S1: D3.1 (K1), J1.4, R4.1, R4.2, U1.11 (S1)
/S2: D6.1 (K1), J1.7, R2.1, R2.2, U1.14 (S2)
/S3: D5.1 (K1), J1.8, R5.1, R5.2, U1.13 (S3)
/SCK: DISP1.7 (SCK), FB1.1
/Teensy_4.1/T26: J1.18, R8.2
/Teensy_4.1/T27: J1.19, R7.2
/Teensy_4.1/T28: J1.20, R6.2
GND: C1.1, C2.1, C3.1, C4.2, C5.2, C6.1, C7.1, C8.1, C9.1, C10.1, C11.1, C12.1, C13.1, C14.1, C15.1, C16.1, C17.1, C18.1, C19.1, C20.1, C21.1, C22.2, C23.2, C24.2, C25.2, C26.2, C27.2, C28.1, C29.2, C30.2, C31.2, C32.2, C33.2, C34.2, C35.2, C36.1, C37.1, C38.1, C39.1, C40.1, C41.1, C42.1, C43.1, D1.2 (K2), D2.2 (K2), D3.2 (K2), D4.2 (K2), D5.2 (K2), D6.2 (K2), D7.2 (K2), D8.2 (K2), D9.2 (K2), D10.2 (K2), D11.2 (K2), D12.2 (K2), D13.2 (K2), D14.2 (K2), D15.2 (K2), D16.2 (K2), D17.2 (K2), D18.2 (K2), D19.2 (K2), D20.2 (K2), D21.2 (K2), D22.2 (K2), D23.2 (K2), D24.1 (A1), D26.2 (K2), D27.2 (K2), D28.2 (K2), D29.2 (K2), D30.2 (K2), D31.2 (K2), D32.2 (K2), D33.2 (K2), D34.2 (K2), D35.2 (K2), D36.2 (K2), D37.2 (K2), D38.2 (K2), D39.2 (K2), DISP1.2 (GND), ENC_MECH1.2 (GND), ENC_MECH1.C (GND), ENC_MECH2.2 (GND), ENC_MECH2.C (GND), ENC_MECH3.2 (GND), ENC_MECH3.C (GND), ENC_MECH4.2 (GND), ENC_MECH4.C (GND), ENC_MECH5.2 (GND), ENC_MECH5.C (GND), ENC_MECH6.2 (GND), ENC_MECH6.C (GND), ENC_MECH7.2 (GND), ENC_MECH7.C (GND), ENC_MECH8.2 (GND), ENC_MECH8.C (GND), ENC_MECH9.2 (GND), ENC_MECH9.C (GND), J1.1, J2.2, J3.2, J4.2, J4.15, J5.2, J6.4, J6.5, J7.2, J8.2, J9.2, U1.12 (GND), U1.15 (~E)
unnamed: C22.1, FB1.2, R7.1
unnamed: D25.1, F1.2
unnamed: D25.2, FB2.2
unnamed: FB4.1, J6.1

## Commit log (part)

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2025-05-08 Ajouter une option pour désactiver l'option RTTI dans la configuration de build pour Teensy
2025-05-08 Réorganiser les inclusions et améliorer la lisibilité du code dans DigitalButton
2025-05-08 Ajouter la classe MidiMapper pour gérer les mappings MIDI et les événements d'encodeur
2025-05-08 Réorganiser les inclusions et améliorer la lisibilité du code dans MidiControllerApp.cpp et MidiControllerApp.hpp
2025-05-08 Réorganiser les inclusions et améliorer la lisibilité du code dans ServiceLocator.hpp et ServiceLocator.cpp, ajouter les méthodes pour récupérer et enregistrer les services ControllerService, InputCo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
2025-05-08 Supprimer les commentaires inutiles dans LearnMidiMapping.cpp et LearnMidiMapping.hpp
2025-05-08 Ajouter la classe MidiMappingFactory pour gérer la création de stratégies de mapping MIDI
2025-05-08 Ajouter la classe SendMidiCCCommand pour gérer l'envoi de messages MIDI CC (Control Change)
2025-05-08 Correction de l'indentation et ajout d'un retour à la ligne à la fin du fichier main.cpp
2025-05-08 Améliorer la gestion des callbacks dans InputSystem en consolidant les fonctions de rappel pour les encodeurs et les boutons, tout en maintenant la compatibilité avec l'InputController.
2025-05-08 Ajouter l'option DISABLE_CONTROLLERS dans les flags de construction pour désactiver les contrôleurs.
2025-05-08 refactor: Remplacer l'EventBus par des callbacks pour la gestion des événements de boutons et d'encodeurs
2025-05-08 docs: Ajouter la documentation du système d'événements avec des détails sur l'organisation, l'utilisation et les types d'événements
2025-05-09 refactor: Optimiser la boucle principale pour limiter la fréquence des mises à jour et permettre le multitâche
2025-05-09 refactor: Ajouter un destructeur pour libérer les ressources et se désabonner du bus d'événements dans MidiControllerApp
2025-05-09 refactor: Supprimer l'ancienne implémentation de Scheduler et ajouter une nouvelle gestion des tâches avec priorités et budget CPU
2025-05-09 refactor: Remplacer les pointeurs bruts par des smart pointers pour une gestion de mémoire améliorée dans MidiSystem
2025-05-09 refactor: Supprimer le fichier .python-version pour nettoyer la configuration du projet
2025-05-10 feat: Ajouter des diagnostics pour l'initialisation et les changements d'état dans ProcessButtons et ProcessEncoders
2025-05-10 refactor: Améliorer les commentaires et la structure d'initialisation dans MidiControllerApp
2025-05-11 feat: Ajouter une analyse détaillée des responsabilités et des dépendances des classes, ainsi qu'un suivi du projet de refactoring
2025-05-11 feat: Implémenter l'adaptateur ServiceLocator et mettre à jour le suivi du projet de refactoring
2025-05-11 Refactor codebase for standardization and error handling improvements
    - Removed Phase 5 report as changes were integrated into documentation.
    - Updated refactoring progress to reflect completion of Phase 5.
    - Refactored ConfigurationSubsystem, InputSubsystem, MidiSubsystem, UISubsystem to use Result<T, E> for error handling.
    - Updated interfaces (IInputSystem, IMidiSystem, IUISystem) to return Result<T, E> in init and configuration methods.
    - Enhanced mock classes (MockInput, MockMidi, MockUI) to implement new Result-based methods.
    - Added StandardChecker tool for code standardization checks, including member naming conventions and Doxygen documentation.
2025-05-11 Refactor: Eliminate ServiceLocatorAdapter and transition to pure dependency injection architecture
    - Removed service_locator_adapter_tests.h and associated tests.
    - Updated test_main.cpp to remove references to ServiceLocatorAdapter tests.
    - Introduced new documentation for the pure dependency injection architecture.
    - Added DeveloperGuide.md to assist developers in extending the MIDI Controller application.
    - Created mocks documentation to explain the use of mocks in testing.
    - Established a new InitializationScript for managing dependency registration.
2025-05-11 refactor: Réorganiser les inclusions et supprimer le débogage périodique dans ProcessEncoders
2025-05-13 refactor: Supprimer les environnements de débogage obsolètes dans platformio.ini
2025-05-13 refactor: Renommer les méthodes sendCc en sendControlChange pour une meilleure clarté et cohérence dans l'API MIDI
2025-05-14 refactor: Implémenter les méthodes de UIEventListener et supprimer ViewManager.cpp
2025-05-14 refactor: Améliorer les messages de débogage et d'initialisation pour une meilleure lisibilité et cohérence
2025-05-15 refactor: Supprimer la section sur l'injection de dépendances et la documentation associée dans le README
2025-05-15 refactor: Supprimer l'écouteur d'événements UI de MidiControllerApp et transférer la gestion à UISubsystem
2025-05-15 refactor: Supprimer les références à TeensyUsbMidi et nettoyer les inclusions dans MidiInHandler, TeensyUsbMidiOut et MidiSubsystem
2025-05-15 refactor: Ajuster la sensibilité des encodeurs et améliorer la gestion des mappings MIDI
2025-05-17 refactor: Améliorer la gestion des messages MIDI en ajustant les limites de taux et en éliminant les doublons
2025-05-22 feat: Add ParameterFocusView for enhanced MIDI parameter visualization
    - Implemented ParameterFocusView to display MIDI parameters with a circular filled interface.
    - Added methods for setting parameters, updating values, and rendering the view.
    - Created example usage in ParameterFocusViewExample.cpp to demonstrate functionality.
    - Updated README documentation to include details on usage, configuration, and integration with MIDI events.
    - Enhanced drawing methods for better visual representation of parameter values.
2025-05-22 refactor: Remplacer initializeEncoderConfigurations par setInputsConfiguration pour une gestion unifiée des configurations
2025-05-25 refactor: Améliorer la gestion des mises à jour d'affichage et simplifier le code des vues
2025-05-25 feat: Ajouter un plan détaillé pour l'intégration de UnifiedConfiguration sans modifier les classes existantes
2025-05-25 Refactor MIDI Mapping System to Use Control Definitions
    - Updated MidiMapper to handle mappings directly from ControlDefinition, simplifying the mapping process.
    - Changed MidiControl to MidiConfig in MidiMapper and related classes for clarity.
    - Modified ProfileManager to manage ControlDefinitions instead of individual MIDI mappings.
    - Enhanced SettingsStore to save and load ControlDefinitions, improving persistence.
    - Adjusted MidiSubsystem to load mappings from ControlDefinitions, streamlining initialization.
    - Refined ProfileController to work with ControlDefinitions, ensuring consistency across the system.
2025-06-15 Ajout du fichier CLAUDE.md avec des conseils et des détails techniques pour le projet de contrôleur MIDI
2025-06-17 feat: Ajouter la configuration LVGL optimisée pour le contrôleur MIDI Teensy 4.1
2025-06-17 chore: Supprimer le plan de refactorisation obsolète pour la configuration unifiée
2025-06-18 Remove the complete display integration plan document and its associated architecture details, including the proposed UI framework, widget system, and development phases for the MIDI Controller 2.0 p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
2025-06-19 feat: Ajouter le widget ParameterWidget pour l'affichage de paramètres MIDI avec animations et labels
2025-06-22 Refactor main.cpp for production mode; remove hardware test code and integrate application initialization
    - Removed commented-out hardware test code and related dependencies.
    - Integrated application initialization logic into setup function.
    - Updated loop function to call app->update() for main application processing.
    - Added error handling for container and application initialization.
    - Updated serial output messages for clarity and consistency.
2025-06-22 feat: Ajouter des logs pour les événements d'encodeur dans MidiMapper
2025-06-22 feat: Ajouter l'adaptateur LvglDisplayPort pour intégrer l'architecture LVGL à l'interface DisplayPort
2025-06-22 refactor: Supprimer la classe ParameterWidgetDemo et ses fichiers associés
2025-06-25 Refactor ParameterWidget to use native lv_arc and UITheme for improved styling and performance
    - Replaced custom configuration structure with direct parameters in the constructor.
    - Integrated UITheme for styling, allowing for dynamic theme application.
    - Simplified label positioning using LVGL's layout system.
    - Added EventBatcher to optimize UI event handling and reduce redraws.
    - Updated MidiControllerApp to initialize and manage EventBatcher for efficient event processing.
    - Introduced DirtyRegionManager to manage redraw regions and optimize rendering performance.
2025-06-27 refactor: Supprimer la classe ProfileController pour simplifier la gestion des profils
2025-07-01 refactor: Améliorer la gestion des widgets MIDI et ajouter le support de la configuration unifiée
2025-07-02 refactor: Mettre à jour les types d'identifiants de bouton et d'encodeur de uint8_t à uint16_t pour une meilleure compatibilité
2025-07-04 feat: Ajout de la permission pour le moniteur de périphérique PIO dans les paramètres
2025-07-05 feat: Ajout de SystemManager pour la gestion centralisée des états et des erreurs du contrôleur MIDI
2025-07-06 feat: Implement DisplayManagerAdapter for optimized display management
    - Added DisplayManagerAdapter class to manage display refresh intervals and force refresh functionality.
    - Integrated with Ili9341LvglBridge for display operations.
    - Introduced methods to set and get refresh intervals.
    feat: Create UISystemAdapter for centralized UI management
    - Developed UISystemAdapter to manage UI components and event processing.
    - Implemented initialization with components and validation of dependencies.
2025-07-10 feat: Mise à jour de l'implémentation du menu avec le widget natif LVGL 9.3.0 et amélioration de la navigation
2025-07-11 feat: Refactorisation de la gestion des entrées avec un InputProcessorManager et des processors spécialisés pour MIDI et navigation
2025-07-11 Remove obsolete files: - Deleted format-all.ps1 script for C/C++ file formatting. - Removed package-lock.json as it is no longer needed. - Eliminated MIGRATION_GUIDE.md as configuration has been unif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
2025-08-02 Update kicad binary files - update 3d models
2025-08-14 Ajout de nouvelles permissions et fonctionnalités dans le fichier de configuration, ainsi que la création d'un bilan final complet du projet KiCad pour le contrôleur MIDI.
2025-08-17 Implement code changes to enhance functionality and improve performance
2025-09-06 update fab files
2025-09-11 Ajout de recommandations d'extensions pour améliorer l'environnement de développement
2025-09-18 Refactor button handling and multiplexing system
    - Updated `platformio.ini` to include new debug flags for multiplexed buttons.
    - Removed `DigitalButton` class and replaced it with a unified button system.
    - Introduced `UnifiedButton` class that utilizes a strategy pattern for pin reading.
    - Implemented `ButtonFactory` to create buttons based on GPIO configuration, supporting both direct and multiplexed pins.
    - Added `IPinReader` interface with `DirectPinReader` and `MuxPinReader` implementations for handling pin reading.
    - Enhanced `MultiplexerManager` to manage multiplexed inputs effectively.
